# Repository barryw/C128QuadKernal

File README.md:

____ _ ____  ___     ___                  _   _  __                     _
      / ___/ |___ \( _ )   / _ \ _   _  __ _  __| | | |/ /___ _ __ _ __   __ _| |
     | |   | | __) / _ \  | | | | | | |/ _` |/ _` | | ' // _ \ '__| '_ \ / _` | |
     | |___| |/ __/ (_) | | |_| | |_| | (_| | (_| | | . \  __/ |  | | | | (_| | |
      \____|_|_____\___/   \__\_\\__,_|\__,_|\__,_| |_|\_\___|_|  |_| |_|\__,_|_|

#### Introduction

This repository holds the following:

- Eagle layout files for the U32 and U35 adapters for a C128. The C128 adapter contains an attiny84 microcontroller that manages A14 and A15 of the 27c512 EEPROM and determines which of the 4 kernals are selected. If the C64 adapter is also installed with the required A14/A15 cable, the attiny84 will also select the kernal of that EEPROM as well.
- Arduino sketch for the attiny84 firmware that controls the selected kernal

#### How does this work?

The C128 contains a 16k C128 Kernal in U35 and a 16k C64 BASIC/Kernal (8k BASIC, 8k Kernal) in U32. With a 64k 27C512 EEPROM, we would have 4 images (4 x 16k = 64k). Often we'd like to use something like JiffyDOS on our 128, but still have the ability to use the stock Kernal for the rare programs that don't work with JiffyDOS.

This requires us to swap the 2 existing 16k ROMS for 2 64k ROMs but give us a way to select which of the 4 kernals to use. Most solutions require a switch or soldering. This solution uses an ATTINY84 microcontroller and the RESTORE key to select our kernal.

The key to all of this is to control the A14 and A15 lines of the 27C512 EEPROM. Ordinarily, a 16k chip only requires 14 address lines (A0-A13). With a 64k chip, we need 16 address lines (A0-A15), but the C128 wasn't designed to deal with them on these ROM chips. With this adapter, we can control these 2 lines to give us 4 kernals (00, 01, 10, 11). The attiny84 microcontroller listens to the RESTORE line to see when we'd like to change kernals. When a new kernal is selected, A14 & A15 are updated to select the kernal and the machine is reset.

#### Building with the Arduino IDE

TODO

#### Generating Gerber files for manufacture

Open the `.brd` files for both C128-Quad-Kernal and C64-Quad-Kernal as you'll need both boards. If you only plan on having kernal swap for the 64 side of the 128, then open the C128-Quad-Kernal brd file. This is the board with the attiny84 chip and it will control A14/A15 of the EEPROM.

Click the button on the toolbar labeled, `Generate CAM Data`. It looks like a factory with a green down arrow. This will generate a ZIP file that you can upload to your board house (I use <a href="https://www.pcbway.com/setinvite.aspx?inviteid=340813" target="_blank">PCBWay</a> and they're awesome!).

#### Loading your EEPROM

The quad kernal boards will only work with a 27C512 64k EEPROM and there's no provision for using a 27C256 EEPROM. That means you can fit 4x16k ROMS onto the chips. If you plan to use multiple kernals for both the 128 and the 64 then you will need 2x 27C512 EEPROM chips (or EPROM chips if you don't mind dealing with UV).

The 128 Kernal uses a single 16k image and nothing special needs to be done other than concatenating 4 separate 16k images. The 64 side of things is a bit different, however. It includes BASIC 2.0 as well as the 64 Kernal. Each 16k slot needs to contain 8k BASIC + 8k KERNAL.

On a Mac, you can create a 64k 128 KERNAL rom like this:

```bash
cat kernal1.rom kernal2.rom kernal3.rom kernal4.rom > kernal128_final.rom
```

For a 64 ROM:

```bash
cat basic1.rom kernal1.rom basic2.rom kernal2.rom basic3.rom kernal3.rom basic4.rom kernal4.rom > basicandkernal64_final.rom
```

If you're only replacing the KERNAL on a C64, then you can duplicate the same BASIC rom:

```bash
cat basic.rom kernal1.rom basic.rom kernal2.rom basic.rom kernal3.rom basic.com kernal4.rom > basicandkernal64_final.rom
```

#### Required cables

The boards will require the following cables:

- 3pin to 3pin F2M dupont connector for the C128's LED. The colors should match the C128 LED which is red, white (ground), black

- 2pin to 2pin F2F dupont connector between the 2 boards A14/A15 headers

- 2pin dupont to mini grabbers. These attach to U63 and U16 for the reset and restore lines. Yellow is reset and white is restore. Attach the white minigrabber end to U16 pin 9 and the yellow minigrabber to U63 pin 2.

#### Installation

Once you have the attiny84 chip programmed, your EEPROMs programmed, the boards populated and the cables built, it's time to install them!

If you're installing both the 128 and 64 boards, first remove the existing chip in U35 and set it aside. Put the board containing the 128 EEPROM in U35 and make sure the header pins are facing the rear of the machine! Do the same for the board containing the 64 EEPROM but for U32.

Next, connect the 2pin-to-2pin cable between the 2 boards. They will need to connect to the A14/A15 header pins on both boards.

Connect the 3pin-to-3pin cable between the 128's LED connector and the LED1, GND, LED2 connector.

Connect the 2pin cable to the RESET/RESTORE header pins. The other end of the RESET cable needs to clip to pin 8 of U63 which is in the back, left corner of the machine. The other end of the RESTORE cable needs to clip to pin 9 of U16 which is toward the front, right of the machine. Don't solder these. Use mini grabbers instead.

#### Operation

The adapter has 2 modes: the default mode will only flash the current KERNAL when the machine is first powered on and then illuminate both LEDs. The alternate mode will keep the current KERNAL illuminated at all times.

To swap modes, hold down the RESTORE key when the machine is powered on. The LEDs will quickly flash in an alternating pattern to show that the mode has changed.

Enter select mode by holding down the RESTORE key until the 128's LED flashes. Release the restore key to begin select mode. The C128's LEDs will light to indicate the current selected KERNAL in binary form. Tap the RESTORE key until the LED shows the binary value of the KERNAL you'd like to use. Finally, hold down the RESTORE key again to save the KERNAL and reset the machine. It should restart with the selected KERNAL.

In the default mode, the LEDs will flash the currently selected KERNAL 5 times on the 128's LEDs. In the case of KERNAL 00 being selected, no LEDs will illuminate.

In the alternate mode, the LEDs will illuminate to show the currently selected KERNAL.

You can also double tap the RESTORE key in quick succession to advance to the next KERNAL.

#### Updating the firmware

The adapter has an ISP port to allow for easy re-programming. You will need something like this: https://www.sparkfun.com/products/11801

Connect the adapter to your programmer with a 6 pin ISP cable and write the firmware out using avrdude or the Arduino IDE.

#### Version 1

There is an earlier version of this board that uses a PIC12F629 located here: https://github.com/barryw/C128QuadKernal/tree/master

This board does not allow for reprogramming the chip in-circuit.

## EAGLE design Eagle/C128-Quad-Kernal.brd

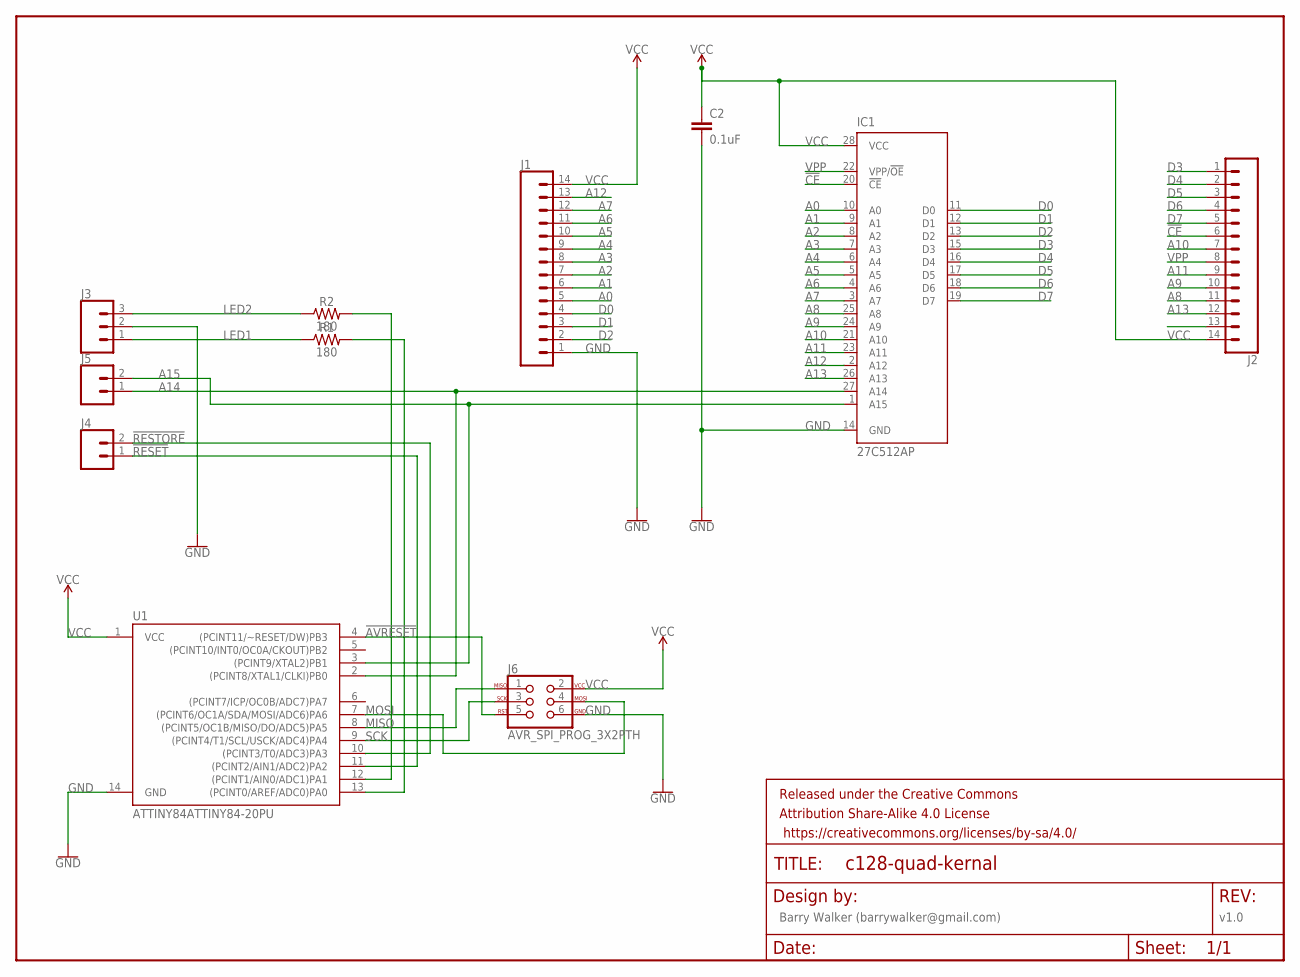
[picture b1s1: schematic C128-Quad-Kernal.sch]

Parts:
C2: 0.1uF; CAP-PTH-SMALL-KIT
FRAME1: FRAME-LETTERNO_PACKAGE; DUMMY
IC1: 27C512AP; DIL28-6
J1, J2: CONN_14; 1X14
J3: CONN_03; 1X03
J4, J5: CONN_02; 1X02
J6: AVR_SPI_PROG_3X2PTH; 2X3
R1, R2: 180; AXIAL-0.3
U1: ATTINY84ATTINY84-20PU; DIP14

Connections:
!AVRESET: J6.5, U1.4 ((PCINT11/~RESET/DW)PB3)
!CE: IC1.20 (!CE), J2.6
!RESET: J4.1, U1.11 ((PCINT2/AIN1/ADC2)PA2)
!RESTORE: J4.2, U1.10 ((PCINT3/T0/ADC3)PA3)
A0: IC1.10 (A0), J1.5
A1: IC1.9 (A1), J1.6
A2: IC1.8 (A2), J1.7
A3: IC1.7 (A3), J1.8
A4: IC1.6 (A4), J1.9
A5: IC1.5 (A5), J1.10
A6: IC1.4 (A6), J1.11
A7: IC1.3 (A7), J1.12
A8: IC1.25 (A8), J2.11
A9: IC1.24 (A9), J2.10
A10: IC1.21 (A10), J2.7
A11: IC1.23 (A11), J2.9
A12: IC1.2 (A12), J1.13
A13: IC1.26 (A13), J2.12
A14: IC1.27 (A14), J5.1, U1.2 ((PCINT8/XTAL1/CLKI)PB0)
A15: IC1.1 (A15), J5.2, U1.3 ((PCINT9/XTAL2)PB1)
D0: IC1.11 (D0), J1.4
D1: IC1.12 (D1), J1.3
D2: IC1.13 (D2), J1.2
D3: IC1.15 (D3), J2.1
D4: IC1.16 (D4), J2.2
D5: IC1.17 (D5), J2.3
D6: IC1.18 (D6), J2.4
D7: IC1.19 (D7), J2.5
GND: C2.2, IC1.14 (GND), J1.1, J3.2, J6.6, U1.14 (GND)
LED1: J3.1, R1.P$1 (1)
LED2: J3.3, R2.P$1 (1)
MISO: J6.1, U1.8 ((PCINT5/OC1B/MISO/DO/ADC5)PA5)
MOSI: J6.4, U1.7 ((PCINT6/OC1A/SDA/MOSI/ADC6)PA6)
unnamed: R1.P$2 (2), U1.13 ((PCINT0/AREF/ADC0)PA0)
unnamed: R2.P$2 (2), U1.12 ((PCINT1/AIN0/ADC1)PA1)
SCK: J6.3, U1.9 ((PCINT4/T1/SCL/USCK/ADC4)PA4)
VCC: C2.1, IC1.28 (VCC), J1.14, J2.14, J6.2, U1.1 (VCC)
VPP: IC1.22 (VPP/!OE), J2.8

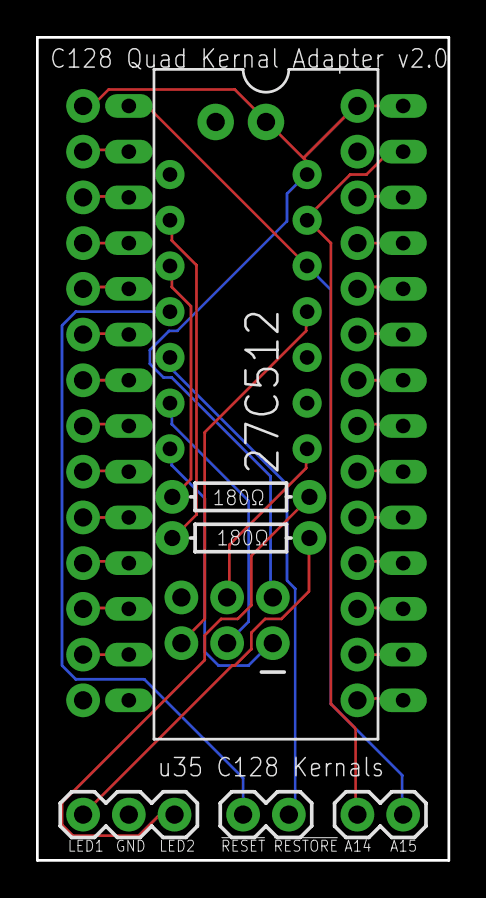
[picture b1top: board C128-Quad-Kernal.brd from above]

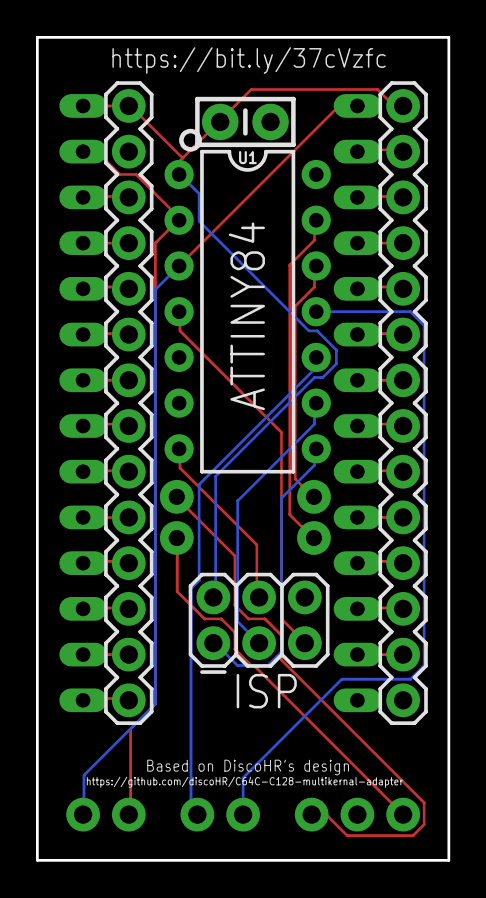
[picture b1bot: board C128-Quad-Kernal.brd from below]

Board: 2 copper layers, 22.9 x 45.7 mm, 12 parts (5 on the bottom side), 38 nets.

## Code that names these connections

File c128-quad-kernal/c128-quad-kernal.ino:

/*
   C128 Quad Kernal

   attiny84 sketch for the C128 Quad Kernal adapter which allows 4 different kernals using the RESTORE key to
   cycle through them. Can be paired with an additional adapter for the U32 C64 BASIC/Kernal to allow 4 separate
   kernals for the C64 portion of a 128 as well.

   Copyright © 2021 Barry Walker

*/

#include <avr/io.h>
#include <EEPROM.h>
#include <AceButton.h>

using namespace ace_button;

const int KERNAL_COUNT      = 4;

// On boot, we flash the selected kernal 5 times on the 128's LEDs
const int FLASH_COUNT       = 5;
const int LONG_FLASH_DELAY  = 250;
const int SHORT_FLASH_DELAY = 100;
const int RESET_DELAY       = 400;

// Default to 2 seconds for a long button press
const int LONG_PRESS_DELAY  = 2000;

const int BOTH_LEDS_ON      = 3;
const int BOTH_LEDS_OFF     = 0;

// Output Pins
const int LED1_PIN          = 1;  // PIN 13
const int LED2_PIN          = 0;  // PIN 12

const int A14_PIN           = 10; // PIN 2
const int A15_PIN           = 9;  // PIN 3

// Input Pins
const int RESTORE_PIN       = 3;  // PIN 10
const int RESET_PIN         = 2;  // PIN 11

// We save the selected kernal in byte 0 of EEPROM
int CURRENT_KERNAL_ID       = 0;

// We save the selected mode in byte 1 of EEPROM
int CURRENT_MODE_ID         = 1;

int currentKernal = 0;

// Keeps track of the state we're in
enum State {
  IDLE,
  SELECT
} state = IDLE;

// Keeps track of the mode we're in. There are 2 modes:
// BRIEF will only show the current kernal on the LEDs
// when the kernal is changed, but keep both LEDs lit the
// rest of the time.
// DETAILED will show the current kernal on the LEDs at
// all times - including when kernal 00 is selected which
// will result in both LEDs being off.
// To change modes, hold down the RESTORE key when you turn
// the machine on. 
enum Mode {
  BRIEF,
  DETAILED
} mode = DETAILED;

AceButton restore(RESTORE_PIN);

void handleEvent(AceButton*, uint8_t, uint8_t);

void setup() {
  mode = loadMode();
  
  // LEDs and address lines are OUTPUTs
  pinMode(LED1_PIN, OUTPUT);
  pinMode(LED2_PIN, OUTPUT);
  pinMode(A14_PIN, OUTPUT);
  pinMode(A15_PIN, OUTPUT);

  // Configure RESTORE and RESET for INPUTs
  // Both lines are active low
  pinMode(RESET_PIN, INPUT);
  pinMode(RESTORE_PIN, INPUT_PULLUP);
  digitalWrite(RESET_PIN, HIGH);

  // If RESTORE is held down at boot, change modes. The change is indicated
  // by quickly alternating the status of the LEDs.
  if(digitalRead(RESTORE_PIN) == 0)
  {
    alternateLEDs(10,50);
    changeMode();
    saveMode(mode);
  }

  restore.getButtonConfig()->setFeature(ButtonConfig::kFeatureLongPress);
  restore.getButtonConfig()->setFeature(ButtonConfig::kFeatureDoubleClick);
  restore.getButtonConfig()->setLongPressDelay(LONG_PRESS_DELAY);
  restore.setEventHandler(handleEvent);

  currentKernal = loadKernal();
  doReset();
}

void loop() {
  restore.check();
}

/*
 * Handle the pressing of the RESTORE key
 */
void handleEvent(AceButton* /*button*/, uint8_t eventType,
                 uint8_t /*buttonState*/) {
  bool longPressed = eventType == AceButton::kEventLongPressed;
  bool clicked = eventType == AceButton::kEventClicked;
  bool doubleClicked = eventType == AceButton::kEventDoubleClicked;

  switch(state) {
    case IDLE:
      if(longPressed) {
        state = SELECT;
        flickerLEDs();
        currentKernal = loadKernal();
        updateLEDs(currentKernal);
      }
      if(doubleClicked) {
        currentKernal = bumpKernal(currentKernal);
        doReset();
      }
      break;

    case SELECT:
      if(longPressed) {
        state = IDLE;
        flickerLEDs();
        doReset();
      }
      if(clicked) {
        currentKernal = bumpKernal(currentKernal);
        updateLEDs(currentKernal);
      }
      break;
  }
}

/*
 * Increment the current kernal
 */
int bumpKernal(int value)
{
  value++;
  if(value == KERNAL_COUNT) value = 0;
  return value;
}

/*
 * Load the saved kernal from EEPROM
 */
int loadKernal()
{
  return loadFromEEPROM(CURRENT_KERNAL_ID);
}

/*
 * Save the current kernal to EEPROM
 */
void saveKernal(int value)
{
  saveToEEPROM(CURRENT_KERNAL_ID, value);
}

/*
 * Retrieve the current mode from EEPROM
 */
int loadMode()
{
  return loadFromEEPROM(CURRENT_MODE_ID);
}

/*
 * Save the current mode to EEPROM
 */
void saveMode(int value)
{
  saveToEEPROM(CURRENT_MODE_ID, value);
}

/*
 * Generic routine to load data from EEPROM
 */
int loadFromEEPROM(int location)
{
  return EEPROM.read(location);
}

/*
 * Generic routine to save data to EEPROM
 */
void saveToEEPROM(int location, int value)
{
  EEPROM.write(location, value);
}

/*
 * Configure A14/A15 to point at the selected kernal
 */
void updateAddressLines(int value)
{
  digitalWrite(A14_PIN, value & 1);
  digitalWrite(A15_PIN, value & 2);
}

/*
 * Update the 128's LEDs to show a value from 0 - 3
 */
void updateLEDs(int value)
{
  digitalWrite(LED1_PIN, value & 1);
  digitalWrite(LED2_PIN, value & 2);
}

/*
 * Flash the 128's LEDs with a value from 0 - 3
 */
void flashLEDs(int value, int count, int ms)
{
  for(int i = 0; i < count; i++)
  {
    blinkLEDs(value, ms);
    delay(ms);
  }
  updateLEDs(BOTH_LEDS_ON);
}

/*
 * Flash the 128's LEDs one time with a value and a delay time
 */
void blinkLEDs(int value, int ms)
{
  updateLEDs(BOTH_LEDS_OFF);
  delay(ms);
  updateLEDs(value);
}

/*
 * Indicate the current kernal on the LEDs by flashing the binary value
 */
void flashCurrentKernal()
{
  flashLEDs(currentKernal, FLASH_COUNT, LONG_FLASH_DELAY);
}

/*
 * Do a quick flicker of the LEDs to show that selection has been accepted
 */
void flickerLEDs()
{
  blinkLEDs(BOTH_LEDS_ON, SHORT_FLASH_DELAY);
}

/*
 * Alternate the LEDs between digital 01 and 02 which just alternates the
 * flashing of the LEDs
 */
void alternateLEDs(int count, int ms)
{
  for(int i = 0; i < count; i++)
  {
    updateLEDs(1);
    delay(ms);
    updateLEDs(2);
    delay(ms);
  }
}

/*
 * Save the kernal to EEPROM, update the address lines and reset the machine
 */
void doReset()
{
  saveKernal(currentKernal);
  updateAddressLines(currentKernal);
  
  digitalWrite(RESET_PIN, LOW);
  pinMode(RESET_PIN, OUTPUT);
  
  delay(RESET_DELAY);
  
  pinMode(RESET_PIN, INPUT);
  digitalWrite(RESET_PIN, HIGH);

  delay(RESET_DELAY);
  
  if(mode == BRIEF)
  {
    flashCurrentKernal();
    updateLEDs(BOTH_LEDS_ON);
  } else {
    updateLEDs(currentKernal);
  }
}

void changeMode()
{
  mode = mode == BRIEF ? DETAILED : BRIEF;
}

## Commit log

2020-12-20 Initial Commit for ATTINY84 version of the board.
2020-12-20 Updated back to use the PIC12F629
2020-12-21 Updated with pretty pictures of the C128 adapter
2020-12-21 Resize images
2020-12-21 Do they need alternate text?!
2020-12-21 Casing probably matters though
2020-12-21 Add images to show kernal indicator on 128's LED
2020-12-24 Code implementation for attiny84
    Also tweaks to the board and schematics
2021-01-01 Add a "mode" which is toggled by holding RESTORE on power up
2021-01-09 Fix for broken reset. It would help to use the right pin.
2021-01-23 Updated images
2021-01-23 Add PCBWay referral link
2021-01-23 Add PCBWay referral
2021-01-23 Add link target
2021-01-23 Add images from Eagle

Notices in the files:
parts and their libraries:
SparkFun-Capacitors: Licensing: Creative Commons ShareAlike 4.0 International - https://creativecommons.org/licenses/by-sa/4.0
SparkFun-Aesthetics: Released under the Creative Commons Attribution Share-Alike 4.0 License
SparkFun-Aesthetics: https://creativecommons.org/licenses/by-sa/4.0
